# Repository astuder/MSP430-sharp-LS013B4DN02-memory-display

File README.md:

Example of using SHARP Memory LCD LS013B4DN04 with MSP430G2553
==============================================================

This is a simple library for TI MSP430G2553 to write characters to SHARP LS013B4DN04
Memory Display using USCI for hardware SPI.

SHARP LS013B4DN04 is a very low power 1.35 inch, 96x96 pixel LCD display. It uses
less than 15 uW when displaying a static image.
http://www.sharpmemorylcd.com/1-35-inch-memory-lcd.html

This code also works with the predecessor LS013B4DN02 and should work with any
display of that series with compatible pinouts.

The project also includes a matching BoosterPack to mount the display on a MSP430 LaunchPad.
More information about the BoosterPack can be found on 43oh:
http://forum.43oh.com/topic/4979-sharp-memory-display-booster-pack/

Pinout MSP430 -> Display
* P1.0:	LED  (VCOM status display)
* P1.5:	SCLK (SPI clock)
* P1.7:	SI   (SPI data)
* P2.0:	DISP (display on/off)
* P2.5:	SCS  (SPI chip select)
* GND:	GND
* VCC:	VDD and VDDA

After adjusting for different pin-out (DISP,SCS), this code also works with the official SHARP LCD BoosterPack by Texas Instruments. 
http://www.ti.com/tool/430BOOST-SHARP96

This code should also work with the Adafruit SHARP Memory Display Breakout
http://www.adafruit.com/products/1393

A library and example for Energia can be found in the Energia subfolder of this project.
This library should also work with Arduino (untested).

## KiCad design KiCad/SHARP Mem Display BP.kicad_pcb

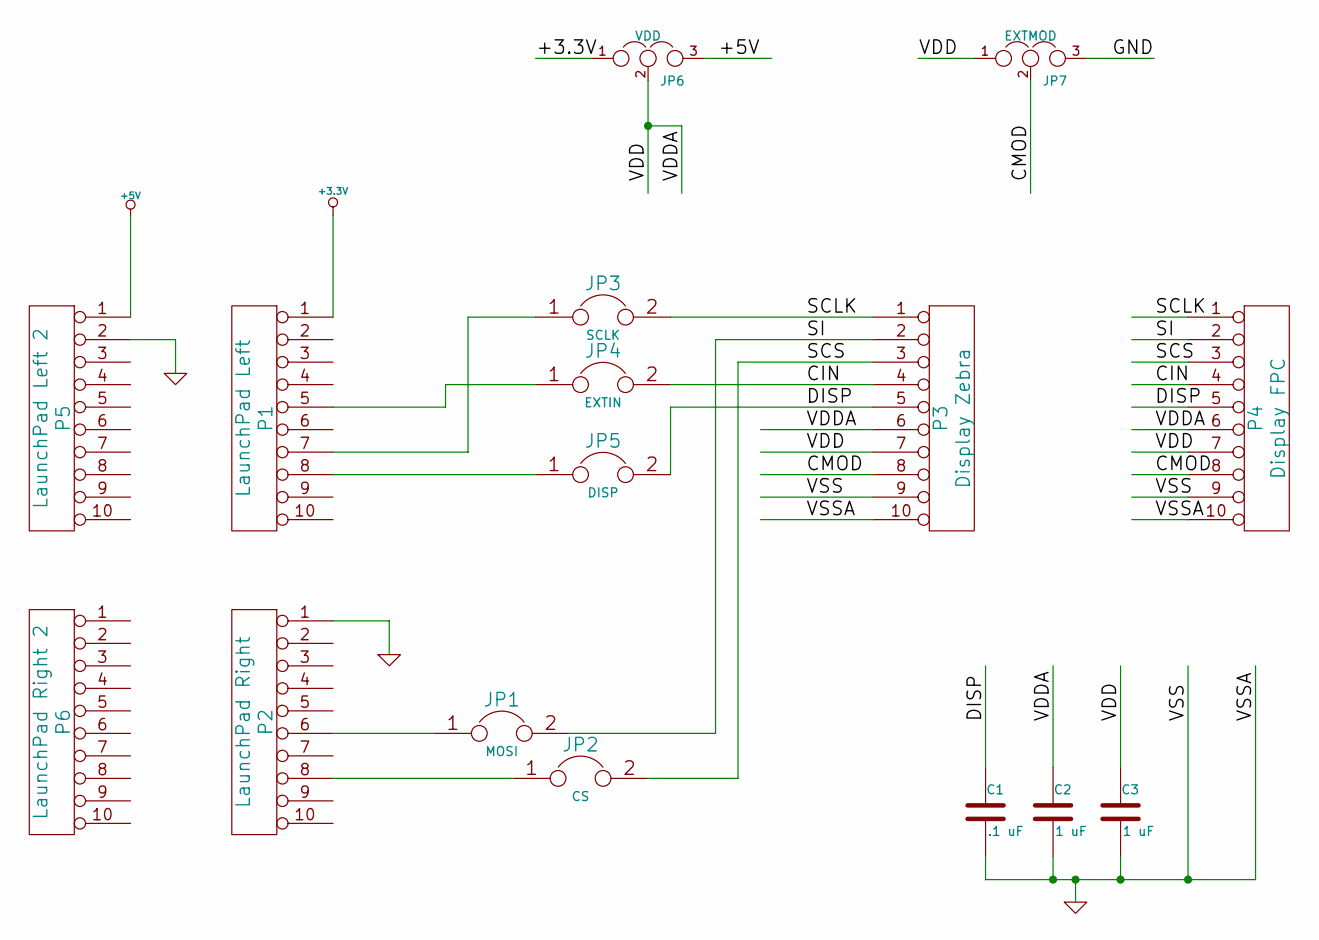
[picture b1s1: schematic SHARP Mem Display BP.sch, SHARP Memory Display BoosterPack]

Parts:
C1: .1 uF
C2, C3: 1 uF
JP1: MOSI
JP2: CS
JP3: SCLK
JP4: EXTIN
JP5: DISP
JP6: VDD
JP7: EXTMOD
P1: LaunchPad Left
P2: LaunchPad Right
P3: Display Zebra
P4: Display FPC
P5: LaunchPad Left 2
P6: LaunchPad Right 2

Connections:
+3.3V: JP6.1, P1.1
+5V: JP6.3, P5.1
/CIN: JP4.2, P3.4, P4.4
/CMOD: JP7.2, P3.8, P4.8
/DISP: C1.1, JP5.2, P3.5, P4.5
/SCLK: JP3.2, P3.1, P4.1
/SCS: JP2.2, P3.3, P4.3
/SI: JP1.2, P3.2, P4.2
/VDD: C2.1, C3.1, JP6.2, JP7.1, P3.6, P3.7, P4.6, P4.7
GND: C1.2, C2.2, C3.2, JP7.3, P2.1, P3.9, P3.10, P4.9, P4.10, P5.2
unnamed: JP1.1, P2.6
unnamed: JP4.1, P1.5
unnamed: JP3.1, P1.7
unnamed: JP5.1, P1.8
unnamed: JP2.1, P2.8

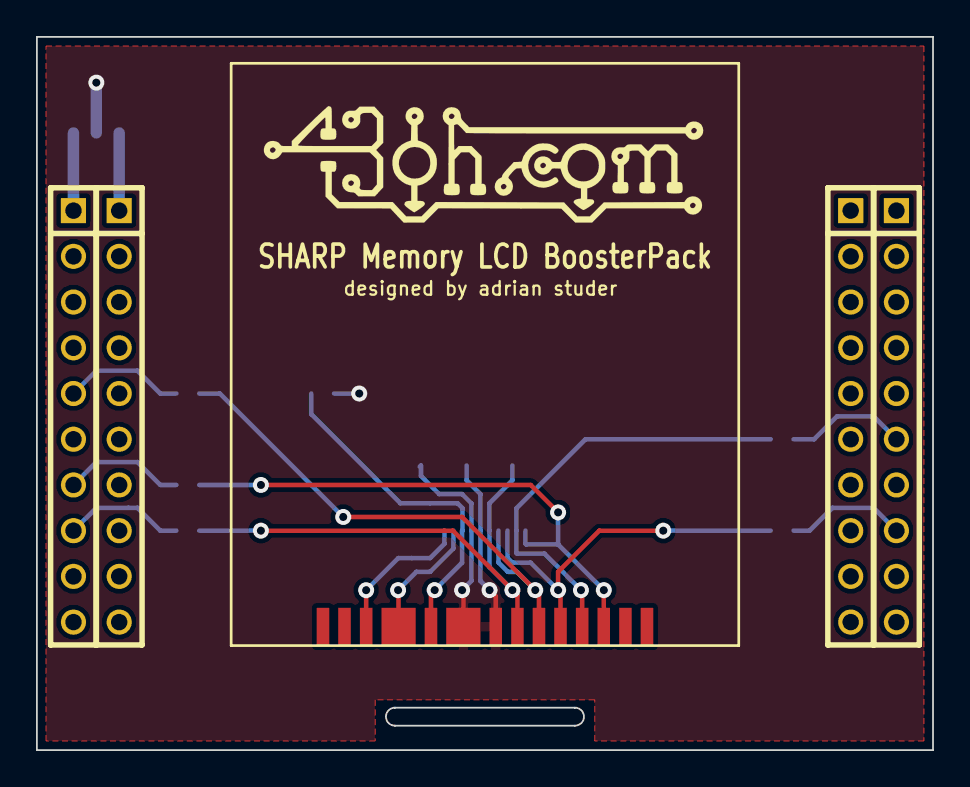
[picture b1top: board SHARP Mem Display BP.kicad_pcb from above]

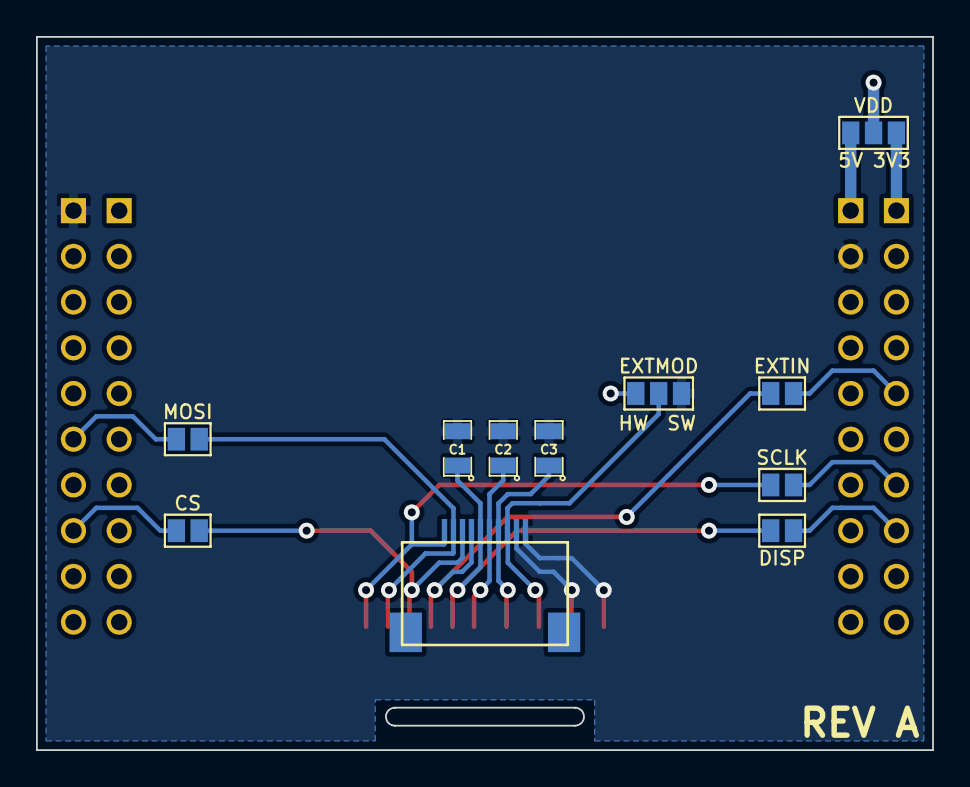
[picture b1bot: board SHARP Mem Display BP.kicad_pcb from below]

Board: 2 copper layers, 49.8 x 39.6 mm, 17 parts (11 on the bottom side), 15 nets.

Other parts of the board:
VAL: 43oh_logo_smaller

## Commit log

2014-01-23 reference to Adafruit breakout board
2014-03-15 G2553 and BoosterPack
2014-04-27 Energia library
2014-04-28 fixed automatic VCOM inversion
2014-04-29 documentation and more
2014-04-29 typo
2014-04-29 readme
2014-04-29 make pulse() save for interrupts
2014-04-29 fixed off()
2014-06-21 added bitmap() function
2014-06-21 added bitmap function
2014-06-21 added invert option to bitmap
2014-06-21 added pulse and bitorder to bitmap method
2014-07-13 added Kicad library cache
2014-09-24 typos
